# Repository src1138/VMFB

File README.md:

A vending machine for birds that rewards them with food when they drop something in a hole. Electronics and enclosure materials cost <100 USD/EUR. I've designed a PCB and PVC pipe enclosure and dispenser (described below). The circuit is not complex, but I think a custom PCB makes it easier for people who are not electronics hobbyists to build this. I've made a few different enclosures ouot of scrap for this, but will share the PVC pipe enclosure details since it's sturdy, waterproof, and the materials can all be found at the hardware store.

There were two main inspirations for me to start and  document this project

- Hans Forsberg (https://www.youtube.com/channel/UCtkv3wuEP-Veur4iYJWkBgA) - designed his own machine and was the first person I learned of that had birds (magpies) bringing items to deposit on thier own
- Josh Klein (https://thecrowbox.com/) - makes his Crowbox designs freely available and supports people who want to build it

# MAIN FEATURES
- portable
- saves power until a warm body is present
- battery or mains powered
- one moving part
- accessible components and materials
- rodents can't break in and get the food
- cheap to build
- customizable

# ELECTRONICS, SENSORS, AND POWER

The circuit is all analog, using four NE555 timers and one LM358 dual op amp. The sensors are all made using IR phototransistors and IR LEDs. The PCB has headers broken out so you can monitor and control it with a microcontroller or SBC. It runs on 5-6VDC and uses ~10mA in standby (~20mA if timer and powerbank keep-alive are enabled), ~250mA when IR LEDs are on and ~400mA when the dispenser motor is running. A 10,000 mAh USB powerbank should last about a week.

- Powerbank Keep-Alive: 555 sinks current every 7-22 seconds for 0.7-2.2 seconds to keep USB power banks on while sensors are in standby - the powerbank keep-alive can be disabled.
- IR LED ON/OFF: 555 keeps the IR LEDs used by the sensors on for 22 seconds after the last PIR trigger
- Op Amps: LM358 used as comparators to adjust the threshold of the sensors and send signals when they are triggered
- Motor Controller: 555 turns on the dispenser vibration motor when the deposit sensors are triggered, tuns it off when the dispense sensor is triggered
- Timed Dispense: 555 dispenses food every 10-100min - timed dispense can be disabled
- Daytimer: Phototransistor that puts the timer in reset while it's dark outside - brightness threshold can be adjusted or disabled (Rev. B)
- PIR Sensor: Sends a signal to turn on the sensor IR LEDs
- Deposit/Dispense Sensors: IR phototransistors and IR LEDs used as proximity sensors to monitor the deposit and dispense chutes
- Hopper Level Sensor: IR phototransistor and IR LED to detect when the food level gets low (Rev. B)
- Monitoring/Control: lines for monitoring and triggering events with an external controller (Rev. B)

# PCB, BOM AND GERBERS

Kicad Files (Github): https://github.com/src1138/VMFB

Gerbers and PCB (PCBWay): https://www.pcbway.com/project/shareproject/Vending_Machine_for_Birds_eda585b3.html

Front

Back

The PCB has footprints for USB type A, USB type B, barrel jack and screw terminal power input. You only need to populate the ones you will use.

In Rev.B Ver.1.0 you need to add a 10K resistor on the EMPTY sensor from the SIGNAL header pin to ground.

The Timer and Powerbank Keep-Alive are not essential and you don't have to populate the parts for them if you don't need/want to use them.

# CRITICAL COMPONENTS

This project uses commodity components, and you can confidently use alternatives with similar specs. There are a few points to keep in mind.

- For the phototransistors, they should have a photocurrent of around 10mA. If they have a lower photocurrent, you should replace the 10K resistors on the non-invertine op amp imputs with a higher value. For  instance, if your phototransistors have a photocurrent of ~1mA, use a 100K resistor intead.
- I use NE555Ps here - you could use other models, but keep in mind that the transistors controlling the IR LEDs (BD139) and motor (TIP41C) need a bit of current to their base. If for instance you use the CMOS 555 that can only source about 10mA, you may need to replace these transistors with ones that have more gain.

# HOW IT WORKS

## States
- Standby - No PIR trigger in the last 22 secs (IR LEDs are off)
- Sensors On - PIR was triggered in the last 22 secs (IR LEDs are on)
- Dispensing - Dispenser motor is on

## Modes

- Normal (dispenses on deposit)
- Timer (dispenses every x minutes AND dispenses on deposit)

## Event Sequence

1. PIR sensor sees a warm body
2. PIR triggers IR LED 555
3. IR LED 555 turn on sensor IR LEDs for 22 secs after last PIR trigger
4. When something is dropped in the deposit hole, the deposit sensor sees it
5. The deposit side of the dual op amp sends a pulse to trigger the motor 555
6. The motor 555 turns on the vibration dispenser motor - it times out after 11 secs
7. When something is dispensed, the dispense sensor sees it 
8. The dispense side of the dual op amp sends a pulse to reset the motor 555
9. The dispenser motor is stopped

When timed dispense is triggered, it sends a signal to turn on the sensor IR LEDs and triggers the motor controller to start the vibration dispenser. When something is dispensed, the motor stops.

# FAILURE MODES
- Deposit sensor jammed: Sensor will not trigger a dispense event until it is unjammed. The sensor uses an inline capacitor to limit the signal to a pulse each time it is triggered.
- Dispense sensor jammed: Vending machine will not dispense until the sensor is unjammed.
- Peanut hopper jammed or empty: Dispense motor will stop after ~10 seconds.

# MONITORING

I was using a Rasperry Pi Zero W with a wide-angle camera module with my vending machine, but I wanted something that drew less power (and was cheaper and more available). I found that the ESP32-CAM module  consumes about 135 MA when streaming video, can be put to sleep (consuming just a few mA) and has 4 GPIO pins available when using the SD-card slot - it can stream/record video and log events from the vending machine, making it all available over wifi or bluetooth.

I'm still in the process of modifying the ESP32-CAM example program to monitor/log events and stream video, record video files to SD, and sleep until the PIR is triggered. I will put this code on Github when it's ready.

# DISPENSER, ENCLOSURE, AND MOUNTING

Dispenser: two-layer vibration platform with offset holes made from 3mm PVC sheet and 15mm M3 brass standoffs. I used a small 24x12mm 2VDC motor attached to the dispenser with brass standoffs and 3mm PVC sheet.

Enclosure: made from 110mm and 50mm PVC pipe and joints, 32mm PVC joints, a 35mm plastic tray and a 1.5l PET bottle. 

Mounting: can be mounted on the ground, horizontal or vertical railing, wooden fence, wall, pole 
The dispenser typically dispenses a peanut or two within 3 seconds. Since it is a vibration dispenser, the enclosure should be level and mounted securely to insure relaible dispensing. 

The dispenser drops peanuts into a funnel made from the top of the PET bottle. There is about 12cm between the two, making it difficult for rodents small enough to get into the machine to get to the food. PVC is tough enough to keep larger rodents from gnawing or breaking thier way in.

# FEED

I used peanuts in the shell to attract birds to the area and shelled peanuts in the vending machine. If you live in an area with lots of pigeons, using peanuts in the shell will not attract them as much since they can't eat them (can't get he shell off) and you have a better chance of attracting corvids. Shelled peanuts are easier to dispense reliably - peanuts in the shell are less dense, more irregular in shape, and jam easily. Dry cat and dog food also works.

# BIRD CONDITIONING

Along with learning and having some fun, the goal is to get a birds to bring something, drop it in a hole, and get a reward. Birds need some conditioning for this, so there are a few phases to progress though to help them figure this out.

## Conditioning Stages
0 - Put food in the area you plan to mount the vending machine to start attracting birds
(1-2 weeks)
1 - Food Provided, Timed Dispense, Deposit Provided
(2-3 weeks)
2 - No Food Provided, Timed Dispense, Deposit Provided
(3-4 months)
3 - No Food Provided, No Timed Dispense, Deposit Provided
(6-8 months)
4 - No Food Provided, No Timed Dispense, No Deposit Provided

Time estimates are based on my own experience over the past year or so, but Phase 3 duration is a guess. As of July 2023 I have not yet seen a bird deposit an item I didn't provide. Unfortunately I had to take my machine down in May due to some new HOA regulations prohibiting feeding the birds in my neighborhood. I plan to redeploy it when I find another suitable location.

# PVC ENCLOSURE 

The PVC enclosure contains the battery, electronics and sensors, dispenser, peanuts, and deposited items. The platform is a 35cm plastic tray for a plant pot, attached to the deposit chute with 4 90-degree brackets, four M4 bolts and two hose clamps.

I used bits of electrical or duct tape to make the PVC pipes and joints fit securely tight. This way it is easy to disassemble/modify/repair. It's a good idea to wrap upward-facing joints to prevent water ingress during heavy rains.

You can load peanuts (or whatever) by unscrewing the top cap and pouring them in. I made two baffles from 3mm PVC sheet to reduce the pressure on the vibration dispenser.

You can unload the deposited items by unscrewing one of the caps on the lower half of the vending machine.

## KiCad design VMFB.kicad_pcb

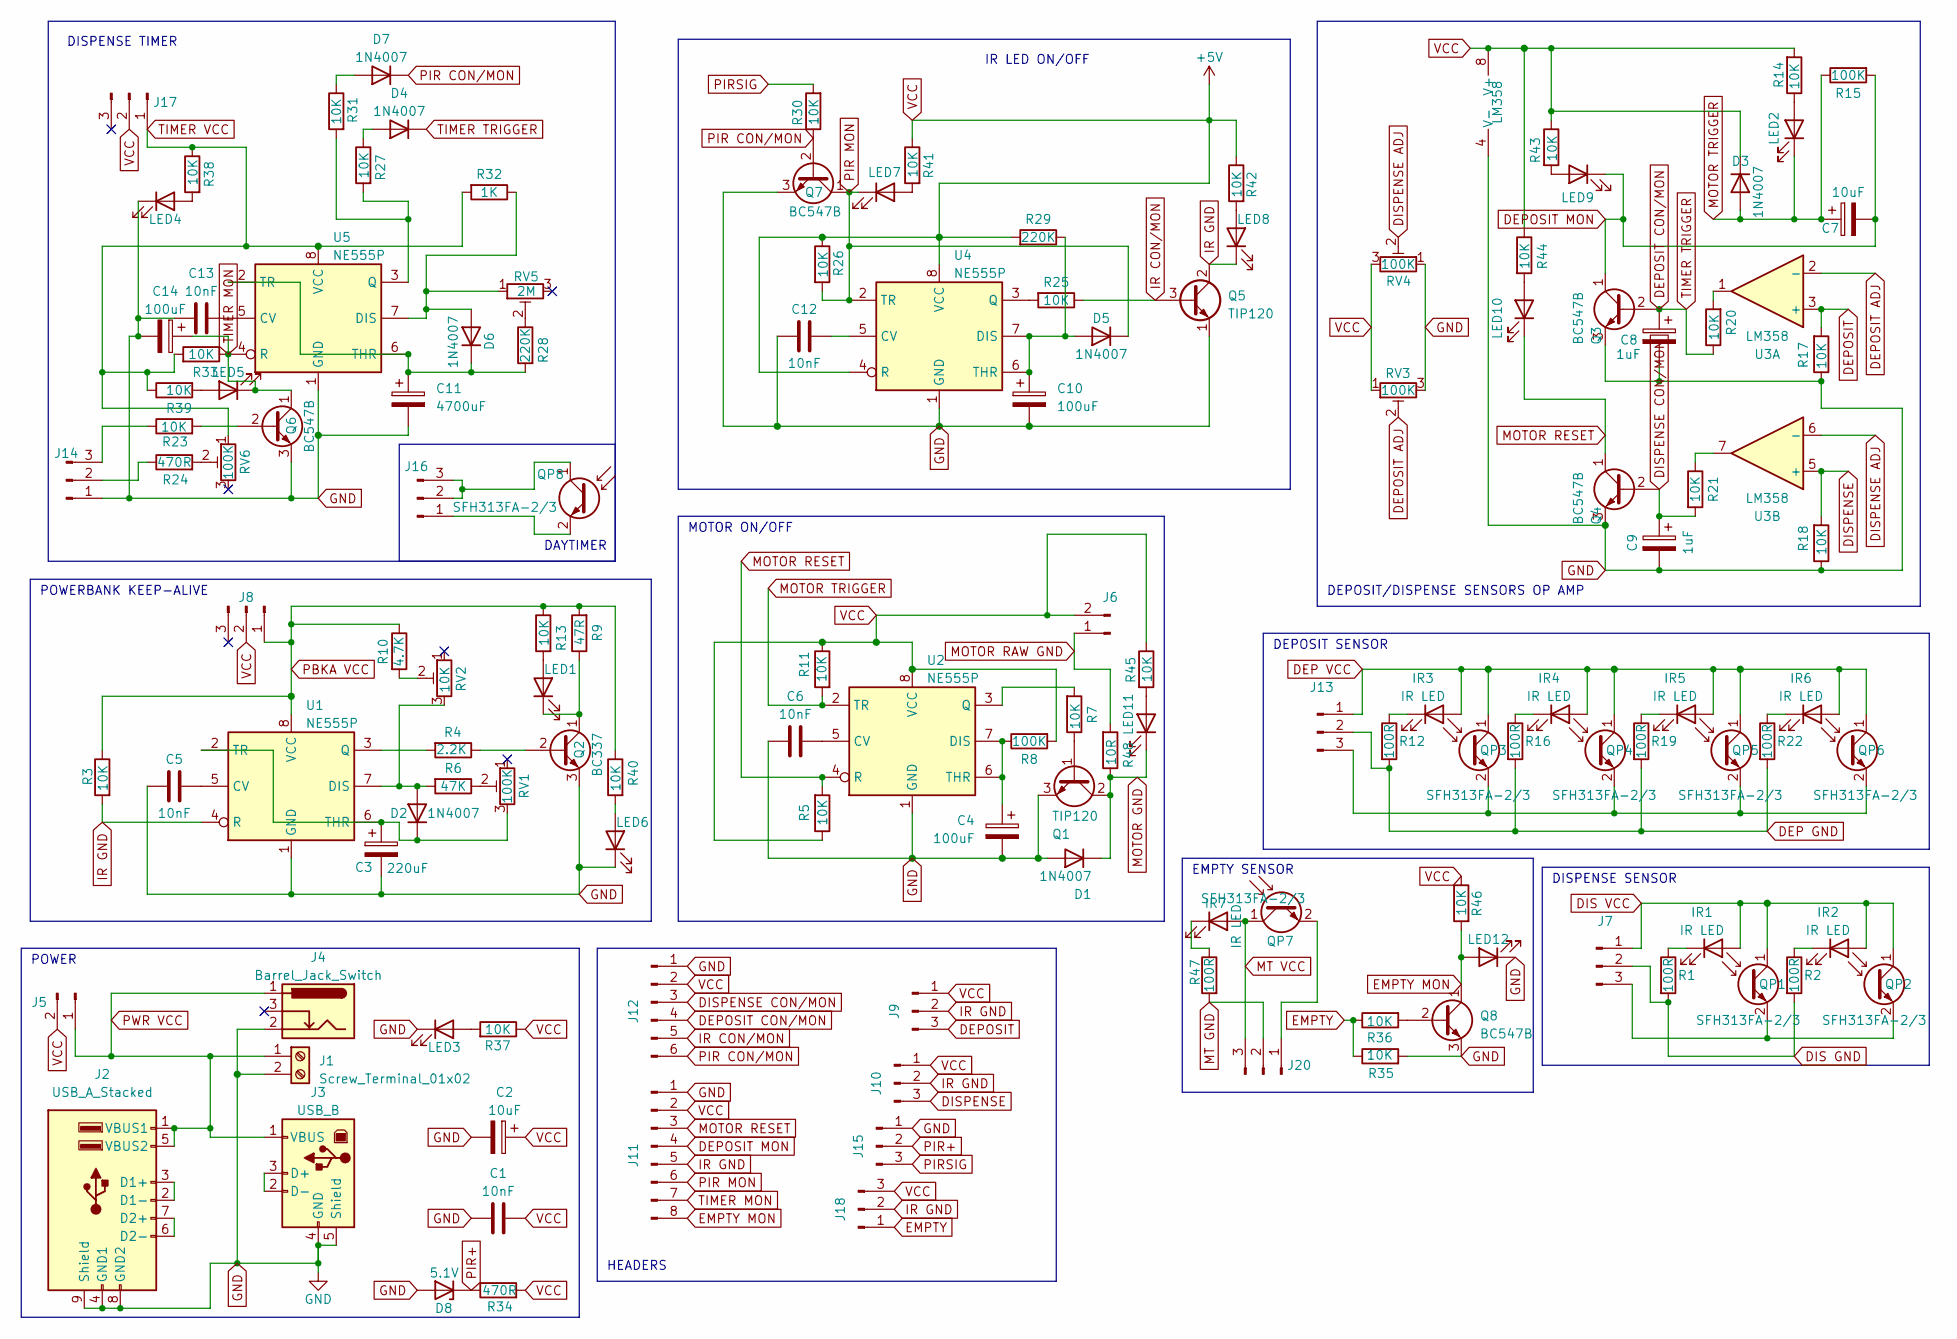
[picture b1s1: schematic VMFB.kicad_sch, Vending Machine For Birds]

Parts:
C1, C5, C6, C12, C13: 10nF; C_Disc_D5.0mm_W2.5mm_P5.00mm
C2, C7: 10uF; CP_Radial_D5.0mm_P2.00mm
C3: 220uF; CP_Radial_D8.0mm_P3.50mm
C4, C10, C14: 100uF; CP_Radial_D6.3mm_P2.50mm
C8, C9: 1uF; CP_Radial_D5.0mm_P2.00mm
C11: 4700uF; CP_Radial_D16.0mm_P7.50mm
D1, D2, D3, D4, D5, D6, D7: 1N4007; D_DO-41_SOD81_P2.54mm_Vertical_KathodeUp
D8: 5.1V; D_DO-41_SOD81_P2.54mm_Vertical_KathodeUp
IR1, IR2, IR3, IR4, IR5, IR6, IR7: IR LED; LED_D5.0mm
J1: Screw_Terminal_01x02; TerminalBlock_Altech_AK300-2_P5.00mm
J2: USB_A_Stacked; USB_A_Wuerth_61400826021_Horizontal_Stacked
J3: USB_B; USB_B_Lumberg_2411_02_Horizontal
J4: Barrel_Jack_Switch; BarrelJack_Horizontal
J5, J6: Conn_01x02_Pin; PinHeader_1x02_P2.54mm_Vertical
J7, J8, J9, J10, J13, J14, J15, J16, J17, J18, J20: Conn_01x03_Pin; PinHeader_1x03_P2.54mm_Vertical
J11: Conn_01x08_Pin; PinHeader_1x08_P2.54mm_Vertical
J12: Conn_01x06_Pin; PinHeader_1x06_P2.54mm_Vertical
LED1, LED2, LED3, LED4, LED5, LED6, LED7, LED8, LED9, LED10, LED11, LED12: Signal LED; LED_D5.0mm
Q1, Q5: TIP120; TO-220-3_Vertical
Q2: BC337; TO-92_Inline_Wide
Q3, Q4, Q6, Q7, Q8: BC547B; TO-92_Inline_Wide
QP1, QP2, QP3, QP4, QP5, QP6, QP7, QP8: SFH313FA-2/3; LED_D5.0mm
R1, R2, R12, R16, R19, R22, R47: 100R; R_Axial_DIN0207_L6.3mm_D2.5mm_P2.54mm_Vertical
R3, R5, R7, R11, R13, R14, R17, R18, R20, R21, R23, R25, R26, R27, R30, R31, R33, R35, R36, R37, R38, R39, R40, R41, R42, R43, R44, R45, R46: 10K; R_Axial_DIN0207_L6.3mm_D2.5mm_P2.54mm_Vertical
R4: 2.2K; R_Axial_DIN0207_L6.3mm_D2.5mm_P2.54mm_Vertical
R6: 47K; R_Axial_DIN0207_L6.3mm_D2.5mm_P2.54mm_Vertical
R8, R15: 100K; R_Axial_DIN0207_L6.3mm_D2.5mm_P2.54mm_Vertical
R9: 47R; R_Axial_DIN0309_L9.0mm_D3.2mm_P2.54mm_Vertical
R10: 4.7K; R_Axial_DIN0207_L6.3mm_D2.5mm_P2.54mm_Vertical
R24, R34: 470R; R_Axial_DIN0207_L6.3mm_D2.5mm_P2.54mm_Vertical
R28, R29: 220K; R_Axial_DIN0207_L6.3mm_D2.5mm_P2.54mm_Vertical
R32: 1K; R_Axial_DIN0207_L6.3mm_D2.5mm_P2.54mm_Vertical
R48: 10R; R_Axial_DIN0414_L11.9mm_D4.5mm_P5.08mm_Vertical
RV1, RV3, RV4, RV6: 100K; Potentiometer_Piher_PT-10-V10_Vertical
RV2: 10K; Potentiometer_Piher_PT-10-V10_Vertical
RV5: 2M; Potentiometer_Piher_PT-10-V10_Vertical
U1, U2, U4, U5: NE555P; DIP-8_W7.62mm
U3: LM358; DIP-8_W7.62mm

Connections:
DEP GND: J13.2, R12.2, R16.2, R19.2, R22.2
DEP VCC: IR3.2 (A), IR4.2 (A), IR5.2 (A), IR6.2 (A), J13.1, QP3.1 (C), QP4.1 (C), QP5.1 (C), QP6.1 (C)
DEPOSIT: J9.3, R17.2, U3.3 (+)
DEPOSIT ADJ: RV3.2, U3.2 (-)
DEPOSIT CON/MON: C8.1, D4.1 (K), J12.4, Q3.2 (B), R20.1
DEPOSIT MON: C7.2, J11.4, LED9.1 (K), Q3.1 (C), R15.2
DIS GND: J7.2, R1.2, R2.2
DIS VCC: IR1.2 (A), IR2.2 (A), J7.1, QP1.1 (C), QP2.1 (C)
DISPENSE: J10.3, R18.2, U3.5 (+)
DISPENSE ADJ: RV4.2, U3.6 (-)
DISPENSE CON/MON: C9.1, J12.3, Q4.2 (B), R21.2
EMPTY: J18.1, R35.1, R36.1
EMPTY MON: J11.8, LED12.2 (A), Q8.1 (C), R46.2
GND: C1.2, C2.2, C3.2, C4.2, C5.2, C6.2, C8.2, C9.2, C10.2, C11.2, C12.2, C13.2, C14.2, D1.2 (A), D8.2 (A), J1.2, J2.4 (GND1), J2.8 (GND2), J2.9 (Shield), J3.4 (GND), J3.5 (Shield), J4.2, J11.1, J12.1, J14.1, J15.1, LED3.1 (K), LED4.1 (K), LED6.1 (K), LED12.1 (K), Q1.3 (E), Q2.3 (E), Q3.3 (E), Q4.3 (E), Q5.1 (E), Q6.3 (E), Q7.3 (E), Q8.3 (E), R17.1, R18.1, R35.2, RV3.3, RV4.1, U1.1 (GND), U2.1 (GND), U3.4 (V-), U4.1 (GND), U5.1 (GND)
IR CON/MON: J12.5, Q5.3 (B), R25.1
IR GND: J9.2, J10.2, J11.5, J18.2, LED8.1 (K), Q5.2 (C), R3.2, U1.4 (R)
MOTOR GND: D1.1 (K), LED11.1 (K), Q1.2 (C), R48.1
MOTOR RAW GND: J6.1, R48.2
MOTOR RESET: J11.3, LED10.1 (K), Q4.1 (C), R5.2, U2.4 (R)
MOTOR TRIGGER: C7.1, D3.2 (A), LED2.1 (K), R11.2, R15.1, U2.2 (TR)
MT GND: J20.2, R47.2
MT VCC: IR7.2 (A), J20.3, QP7.1 (C)
unnamed: D2.2 (A), R6.2, RV2.3, U1.7 (DIS)
unnamed: C3.1, D2.1 (K), RV1.3, U1.2 (TR), U1.6 (THR)
unnamed: D4.2 (A), R27.1
unnamed: C10.1, D5.2 (A), R29.1, U4.6 (THR), U4.7 (DIS)
unnamed: D6.2 (A), R32.1, RV5.1, U5.7 (DIS)
unnamed: C11.1, D6.1 (K), R28.2, U5.2 (TR), U5.6 (THR)
unnamed: D7.2 (A), R31.1
unnamed: IR1.1 (K), R1.1
unnamed: IR2.1 (K), R2.1
unnamed: IR3.1 (K), R12.1
unnamed: IR4.1 (K), R16.1
unnamed: IR5.1 (K), R19.1
unnamed: IR6.1 (K), R22.1
unnamed: IR7.1 (K), R47.1
unnamed: J2.2 (D1-), J2.3 (D1+)
unnamed: J2.6 (D2-), J2.7 (D2+)
unnamed: J3.2 (D-), J3.3 (D+)
unnamed: J7.3, QP1.2 (E), QP2.2 (E)
unnamed: J13.3, QP3.2 (E), QP4.2 (E), QP5.2 (E), QP6.2 (E)
unnamed: J14.2, R24.1
unnamed: J14.3, R23.1
unnamed: J16.1, QP8.2 (E)
unnamed: J16.2, J16.3, QP8.1 (C)
unnamed: J20.1, QP7.2 (E)
unnamed: LED1.2 (A), R13.2
unnamed: LED1.1 (K), Q2.1 (C), R9.1
unnamed: LED2.2 (A), R14.1
unnamed: LED3.2 (A), R37.2
unnamed: LED4.2 (A), R38.2
unnamed: LED5.2 (A), R39.2
unnamed: LED6.2 (A), R40.2
unnamed: LED7.2 (A), R41.2
unnamed: LED8.2 (A), R42.2
unnamed: LED9.2 (A), R43.2
unnamed: LED10.2 (A), R44.2
unnamed: LED11.2 (A), R45.2
unnamed: Q1.1 (B), R7.1
unnamed: Q2.2 (B), R4.1
unnamed: Q6.2 (B), R23.2
unnamed: Q8.2 (B), R36.2
unnamed: R6.1, RV1.2
unnamed: R10.2, RV2.2
unnamed: R20.2, U3.1
unnamed: R21.1, U3.7
unnamed: R24.2, RV6.2
unnamed: R28.1, RV5.2
unnamed: C5.1, U1.5 (CV)
unnamed: R4.2, U1.3 (Q)
unnamed: C6.1, U2.5 (CV)
unnamed: C4.1, R8.1, U2.6 (THR), U2.7 (DIS)
unnamed: R7.2, U2.3 (Q)
unnamed: C12.1, U4.5 (CV)
unnamed: R25.2, U4.3 (Q)
unnamed: C13.1, U5.5 (CV)
unnamed: R27.2, R31.2, U5.3 (Q)
PBKA VCC: J8.1, R3.1, R9.2, R10.1, R13.1, R40.1, U1.8 (VCC)
PIR CON/MON: D7.1 (K), J12.6, Q7.2 (B), R30.1
PIR MON: D5.1 (K), J11.6, LED7.1 (K), Q7.1 (C), R26.2, U4.2 (TR)
PIR+: D8.1 (K), J15.2, R34.1
PIRSIG: J15.3, R30.2
PWR VCC: J1.1, J2.1 (VBUS1), J2.5 (VBUS2), J3.1 (VBUS), J4.1, J5.1
TIMER MON: C14.1, J11.7, LED5.1 (K), Q6.1 (C), R33.1, U5.4 (R)
TIMER VCC: J17.1, R32.2, R33.2, R38.1, R39.1, RV6.1, U5.8 (VCC)
VCC: C1.1, C2.1, D3.1 (K), J5.2, J6.2, J8.2, J9.1, J10.1, J11.2, J12.2, J17.2, J18.3, R5.1, R8.2, R11.1, R14.2, R26.1, R29.2, R34.2, R37.1, R41.1, R42.1, R43.1, R44.1, R45.1, R46.1, RV3.1, RV4.3, U2.8 (VCC), U3.8 (V+), U4.4 (R), U4.8 (VCC)

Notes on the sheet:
DISPENSE SENSOR
POWER
DEPOSIT SENSOR
MOTOR ON/OFF
EMPTY SENSOR
DISPENSE TIMER
HEADERS
POWERBANK KEEP-ALIVE
IR LED ON/OFF
DAYTIMER
DEPOSIT/DISPENSE SENSORS OP AMP

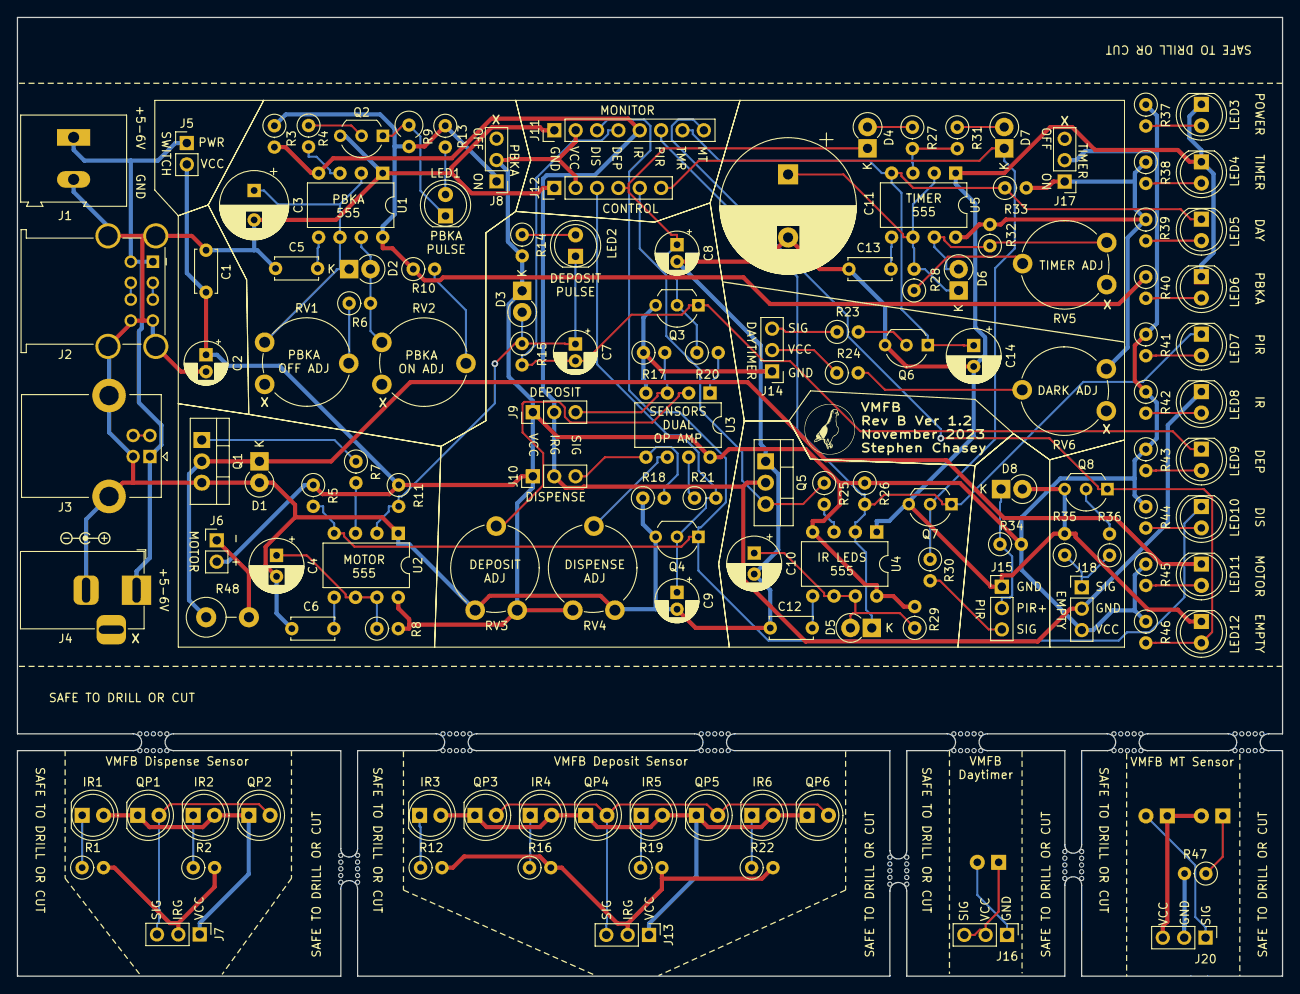
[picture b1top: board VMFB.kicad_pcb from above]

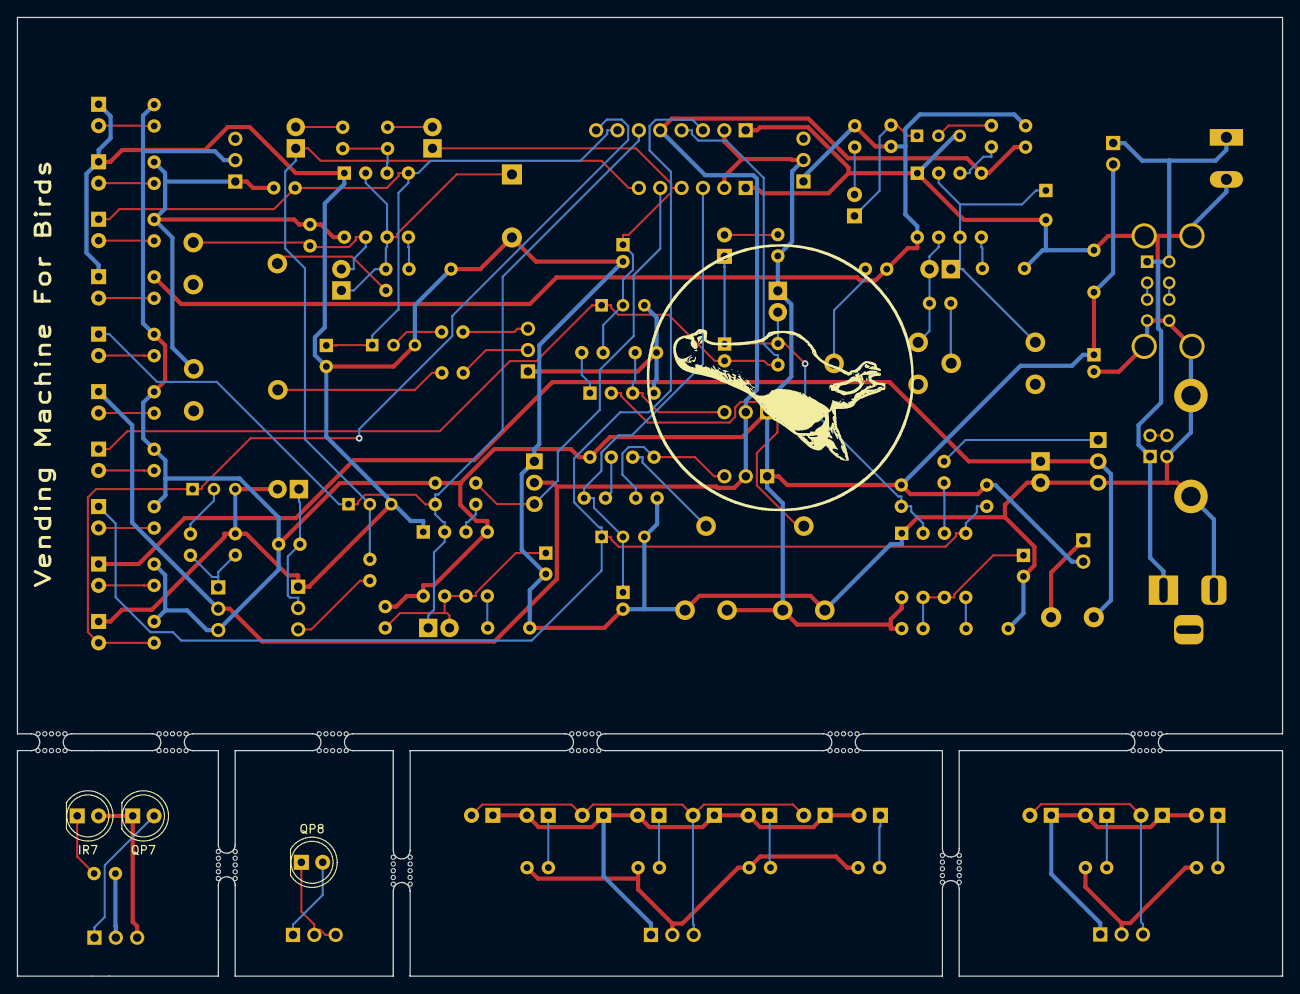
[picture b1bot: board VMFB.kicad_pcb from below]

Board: 2 copper layers, 150.4 x 114.0 mm, 138 parts (4 on the bottom side), 86 nets.

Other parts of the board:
DIRTY BIRD: LOGO
Polarity: Center Pos; LOGO
Small Dirty Bird: LOGO

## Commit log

2023-05-09 Adding VMFB Kicad project/schematic/pcb files
2023-05-09 Adding prl, xml and sym project files
2023-05-09 Update README.md
    Adding general info about the circuit.
2023-05-09 Update README.md
    corrected dispense timeout (24 -> 11 secs)
2023-05-10 adding parts cache file
2023-05-17 Added 1uf cap on the dispense transistor base to prevent triggering on power-up.
2023-05-22 Swapped PIR+ and GND to better accomodate common PIR pinouts.
2023-05-23 Added 100K bleeder resistor across the pulse-shortening cap C7
2023-05-23 changed external header to 6-pin with pinout to match most 4-channel level shifters, removed 2 unnecessary 10K reset resistors from timer and IR power 555s
2023-05-23 added another 1uf cap across the dispense sensor so like the dispense sensor it won't trigger on power up.
2023-05-23 added resistor and diode to turn IR LEDs on when the timer triggers so the dispense sensors can stop the motor
2023-05-23 a few small tweaks, connecting the switch pin of the barrel jack to ground
2023-05-23 tweaked silkscreen labels
2023-05-29 changed signal LED resistors to 10K from 1K.
2023-06-02 Update README.md
    Added link to PCBWay shared project for gerbers and BOM.
2023-06-02 Update README.md
    Adding some images of the board.
2023-06-02 Update README.md
    Replacecd blurry side view pic.
2023-06-04 added monitoring-only header, moved IR LED switch transistor from VCC to GND and removed a pin from the sensor headers (no need for separate VCC for the IR LEDS), 100R to 47R on Q$ base, 47R to 22R o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
2023-06-05 moved dispense monitoring directly to the collector of Q2 so you can tell if it's jammed
2023-06-05 updated version to 1.3
2023-06-05 updated control header label and changed footprint for BC547 two commits ago
2023-06-08 added LDR-based light sensor to turn off timed dispense when the sun sets
2023-06-12 improvements to the daytimer, and added an LED so you can see the status
2023-06-12 minor adjustments to the daytimer
2023-06-13 more adjustments to the daytimer
2023-06-14 more adjustments to the daytimer and cleaned up schematic a bit
2023-06-15 Update README.md
    added unabbreviated project name to readme.
2023-06-16 added box labels to schematic, bit more tweaking on the PCB
2023-06-20 schematic rearranging, swapped LDR for phototransistor on the Daytimer, added peanut hopper empty sensor, pcb rearranging
2023-06-20 tweakedcomponent placement on Daytimer
2023-06-21 marked different modules on the PCB, reannotated, small placement adjustments
2023-06-23 schematic cleanup, pcb tweaking
2023-06-25 schemati and pcb tweaking
2023-06-26 schematic and pcb tweaking
2023-06-27 removed 10K resistor to ground fromo empty sensor
2023-06-27 removed transistor/resistor disabline PBKA when IR is on = grounding this along with the IR and signal LEDs instead of using another transistor
2023-06-28 small tweaks and corrected 'Deposit Pulse' LED label (was 'Dispense Pulse')
2023-07-03 added transistor to the PBKA
2023-07-03 added logo
2023-07-04 fixed timer connection to trigger IR LEDs
2023-07-04 more cleanup
2023-07-10 Added space for 1.6mm tab routing
    Added space for tab routing so PCBway doesn't have to modify the board before fabrication. Makes ordering easier, slightly cheaper and looks nicer.
2023-07-10 Delete ~VMFB.kicad_sch.lck
    removing lock file
2023-07-11 more pcb tweaks
2023-07-11 Update LICENSE
    Changing license to GNU GENERAL PUBLIC LICENSE Version 3, 29 June 2007
2023-07-12 changing route paths from 1.6mm to 2.0mm - PCBWay says min of 1.6, but boards I have received have 2.0mm wide panel routes
2023-07-16 Update README.md
    Updated to reflect R3v. B V 1.0 changes.
2023-07-16 Update README.md
    Small formatting fix.
2023-07-17 added 2mm tab routes with break holes to the pcb based on what PCBWay has done to panelize previous versions
2023-07-27 Fixed some component names.
2023-07-27 Update README.md
    Added info about critical components.
2023-08-02 fixed dark sensor - connected BC547B emitter to IR GND net (was connected to ground, so base was always triggering the transistor a little due to IR GND being .7 volts above actual ground)
2023-08-02 fixed dark sensor - added 10K resistor grounding the phototransistor output
2023-08-03 changed 1K resistor on empty sensor to 100R
2023-08-03 Delete fp-info-cache
    Removing fp-info-cache file - not required.
2023-08-04 PCB tweaking
    Changed R7 footprint to 11.5x4.5. Marked off Dark Sensor and moved logo and version. Flipped R11.
2023-08-06 Added routing
2023-08-14 removed unnecessary 470R from Daytimer module
2023-08-14 adding routes
2023-08-15 changed 470R to 1K on the Daytimer
2023-08-15 Update README.md
    Added failure mode notes
2023-08-19 updated routing - no vias
2023-08-23 tweaked routing
2023-08-24 Update README.md
    Updated PCB images to latest version RevB V1.1.
2023-09-05 adding monitor file for motioneyeos to display status (PIR/Sensors/Timer/Feed Hopper) - the file needs to be executable and goes in /data/etc/
2023-09-06 added logging
2023-09-06 adding motioneyeos action button scripts to manually turn the sensors on or dispense a peanut by clicking a button
2023-09-06 some debugging,code is messy - not fast enough to catch deposit and dispense events
2023-09-06 some more debugging
2023-09-07 even more debugging - some pins had to be changed
2023-09-07 working ok - if you use pins 12 and 13 for the manual sensor activation and dispensing, you should add this to your config.txt: gpio=12,16=op,dl
2023-09-07 added deposit and dispense sensor jam detection
2023-09-07 restored 1 second delay
2023-09-12 moved logging to python for interrupt support, turning off hdmi in userinit.sh
2023-09-12 updating monitor to just read the file written by the python script
2023-09-12 only logging deposit and dispense with python, put the rest in the monitor_1 shell script
2023-09-12 running VMFB_logger.py as a background process on startup
2023-09-13 record video while the sensors are on
2023-09-13 split logging from monitor
2023-09-13 debugging
2023-09-13 buttons to disable/enable the camera
2023-09-14 tweaks
2023-09-14 adding example camera and motion config files
2023-09-14 moving files
2023-09-14 adding script to schedule camera enable/disable
2023-09-14 renaming
2023-09-14 adding camera enable/disable scheduler
2023-09-14 debugging camera scheduler
2023-09-18 more debugging, added timer script
2023-09-18 debugging camera on/off scheduler
2023-09-18 Create README_motioneye.md
    Add some documentation about setting up and using the scripts.
2023-11-21 replaced TIP41 and BC137 with TIP120s, changed empty sensor from beam break to proximity
2023-12-07 updating netclasses, adding routing
2023-12-07 cleaned up tracks
2024-01-06 spelling and formatting
